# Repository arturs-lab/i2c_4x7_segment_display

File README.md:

# i2c_4x7_segment_display
4 digit 7 segment led display with i2c interface. Accepts data packets of two bytes, MSB first and displays value.

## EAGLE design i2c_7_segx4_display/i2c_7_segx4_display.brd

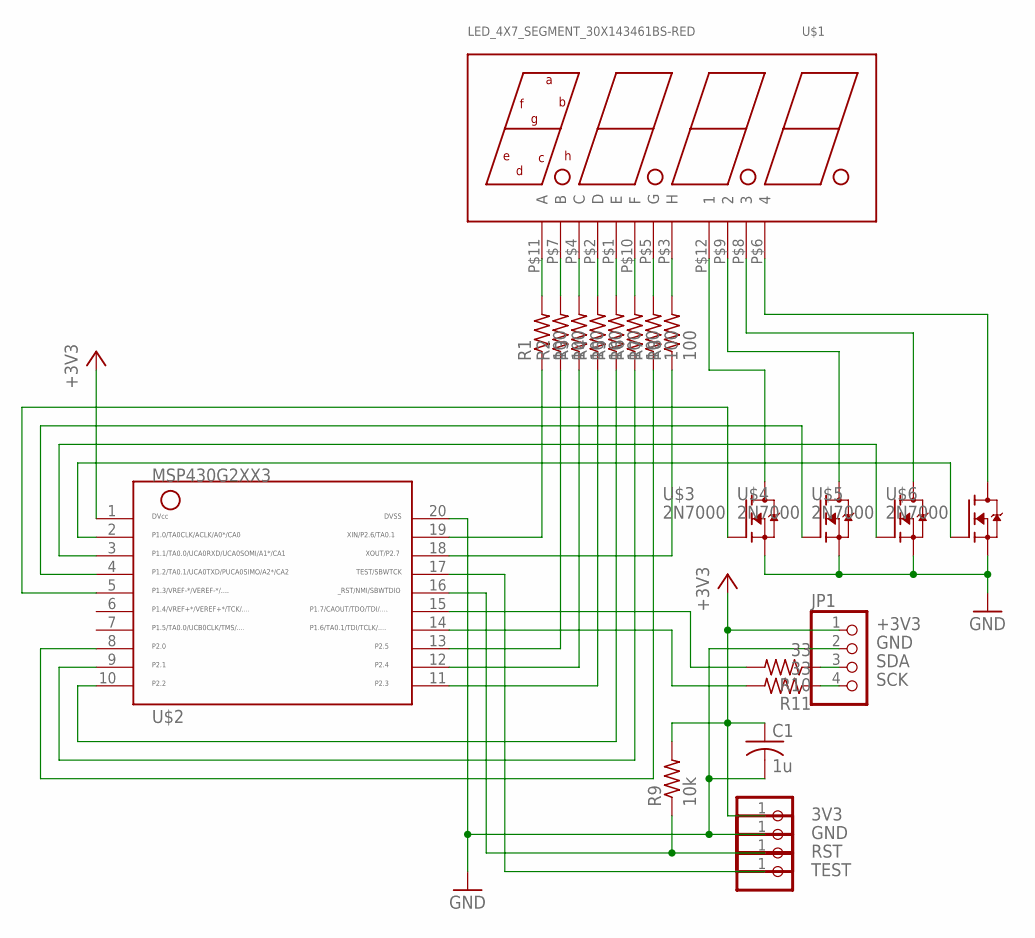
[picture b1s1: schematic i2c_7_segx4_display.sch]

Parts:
3V3: PINHD-1X1; 1X01
C1: 1u; C0805K
GND: PINHD-1X1; 1X01
JP1: PINHD-1X4; 1X04
R1, R2, R3, R4, R5, R6, R7, R8: 100; R0603
R9: 10k; R0603
R10, R11: 33; R0603
RST: PINHD-1X1; 1X01
TEST: PINHD-1X1; 1X01
U$1: LED_4X7_SEGMENT_30X143461BS-RED; LED_4X7_SEGMENT_30X14
U$2: G2553; PW20
U$3, U$4, U$5, U$6: 2N7000; SOT23

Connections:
+3V3: 3V3.1, C1.1, JP1.1, R9.2, U$2.1
GND: C1.2, GND.1, JP1.2, U$2.20, U$3.2 (S), U$4.2 (S), U$5.2 (S), U$6.2 (S)
unnamed: R1.2, U$1.P$11 (A)
unnamed: R2.2, U$1.P$7 (B)
unnamed: R3.2, U$1.P$4 (C)
unnamed: R4.2, U$1.P$2 (D)
unnamed: R5.2, U$1.P$1 (E)
unnamed: R6.2, U$1.P$10 (F)
unnamed: R7.2, U$1.P$5 (G)
unnamed: R8.2, U$1.P$3 (H)
unnamed: R1.1, U$2.19
unnamed: R2.1, U$2.13
unnamed: R3.1, U$2.12
unnamed: R4.1, U$2.11
unnamed: R8.1, U$2.18
unnamed: R5.1, U$2.10
unnamed: R6.1, U$2.9
unnamed: R7.1, U$2.8
unnamed: U$2.2, U$6.1 (G)
unnamed: U$1.P$12 (1), U$3.3 (D)
unnamed: U$1.P$9 (2), U$4.3 (D)
unnamed: U$1.P$8 (3), U$5.3 (D)
unnamed: U$1.P$6 (4), U$6.3 (D)
unnamed: U$2.3, U$5.1 (G)
unnamed: U$2.4, U$4.1 (G)
unnamed: U$2.5, U$3.1 (G)
unnamed: R9.1, RST.1, U$2.16
unnamed: TEST.1, U$2.17
SCK: JP1.4, R11.1
SCKX: R11.2, U$2.14
SDA: JP1.3, R10.1
SDAX: R10.2, U$2.15

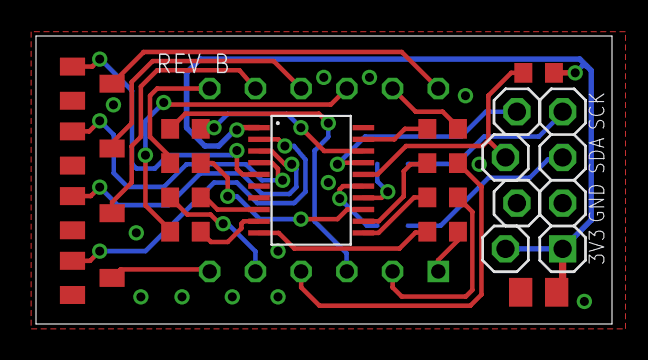
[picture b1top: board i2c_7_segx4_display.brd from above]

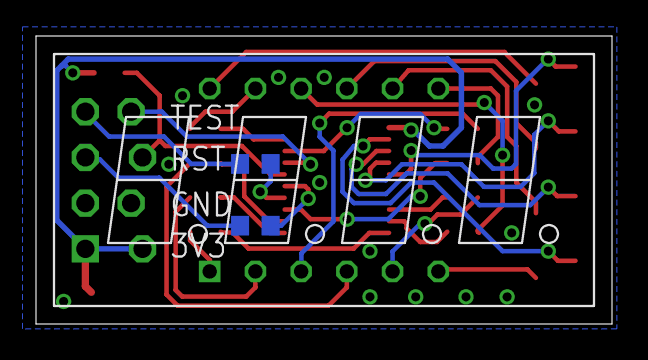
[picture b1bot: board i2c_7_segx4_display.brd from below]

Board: 2 copper layers, 32.0 x 16.0 mm, 23 parts (3 on the bottom side), 32 nets.
